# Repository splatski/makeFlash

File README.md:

# makeFlash
Soldering workshop board for Hobart Makers

# New Repository
Repositry is now at https://gitlab.com/HobartMakers/makeFlash

## Licence
Licensed under the TAPR Open Hardware License (www.tapr.org/OHL). The "license" folder within this repository also contains a copy of this license in plain text format.

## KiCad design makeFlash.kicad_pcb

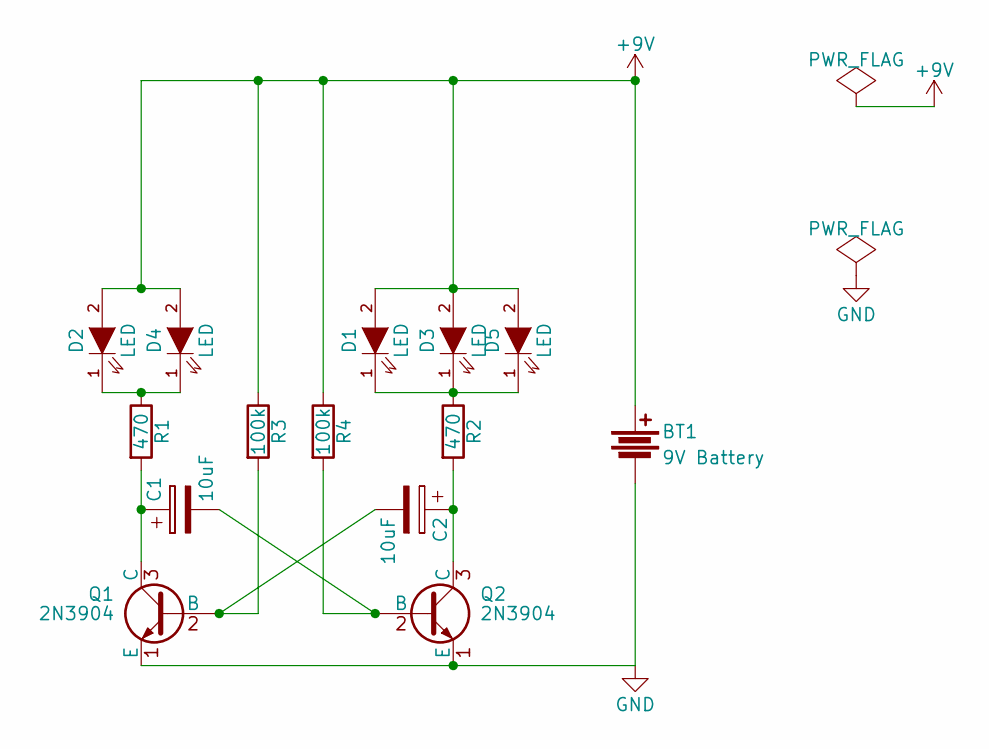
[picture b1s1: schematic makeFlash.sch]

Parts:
BT1: 9V Battery; Pin_Header_Straight_1x02_Pitch2.54mm
C1, C2: 10uF; CP_Radial_D5.0mm_P2.50mm
D1, D2, D3, D4, D5: LED; LED_Rectangular_W5.0mm_H2.0mm
Q1, Q2: 2N3904; TO-92_Rugged
R1, R2: 470; Resistor_Horizontal_RM10mm
R3, R4: 100k; Resistor_Horizontal_RM10mm

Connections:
+9V: BT1.1, D1.2 (A), D2.2 (A), D3.2 (A), D4.2 (A), D5.2 (A), R3.1, R4.1
GND: BT1.2, Q1.1 (E), Q2.1 (E)
unnamed: C1.1, Q1.3 (C), R1.2
unnamed: C1.2, Q2.2 (B), R4.2
unnamed: C2.1, Q2.3 (C), R2.2
unnamed: C2.2, Q1.2 (B), R3.2
unnamed: D1.1 (K), D3.1 (K), D5.1 (K), R2.1
unnamed: D2.1 (K), D4.1 (K), R1.1

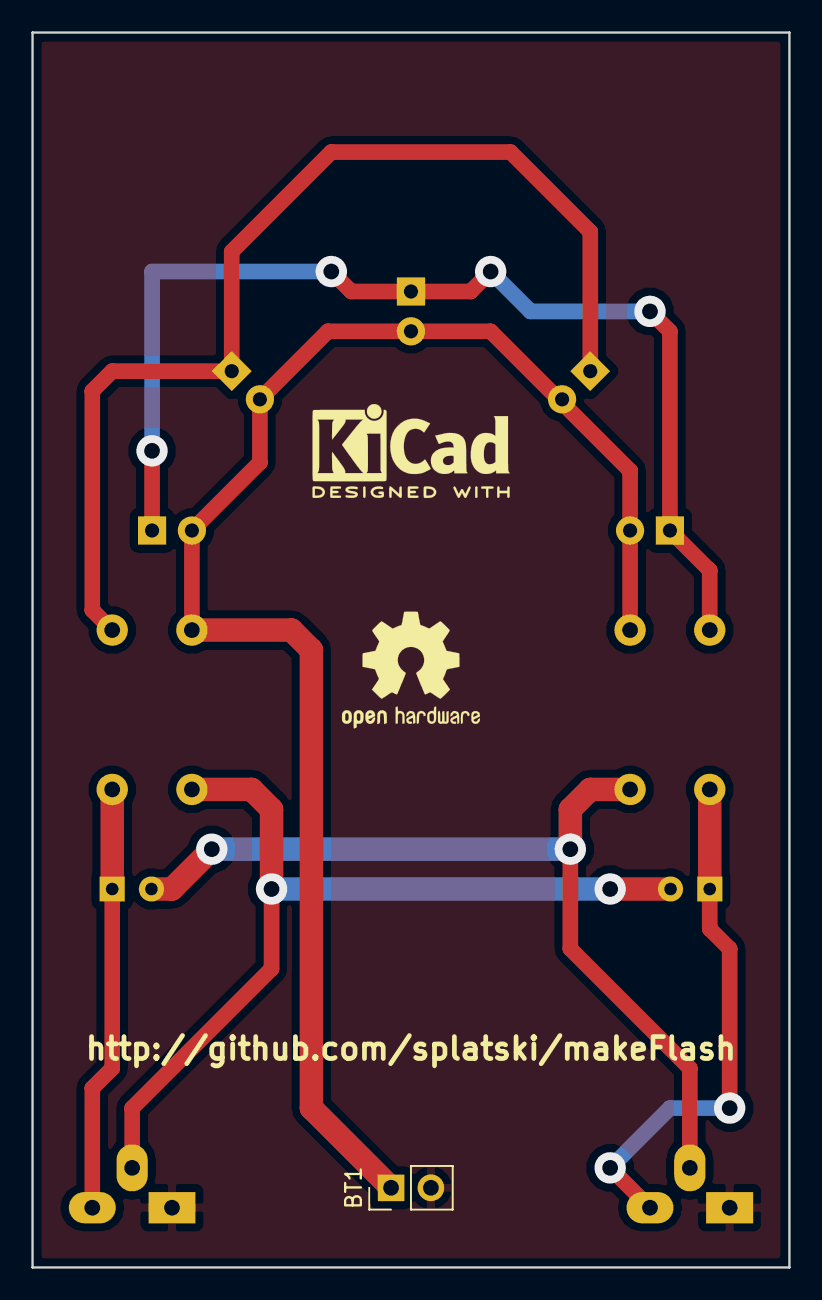
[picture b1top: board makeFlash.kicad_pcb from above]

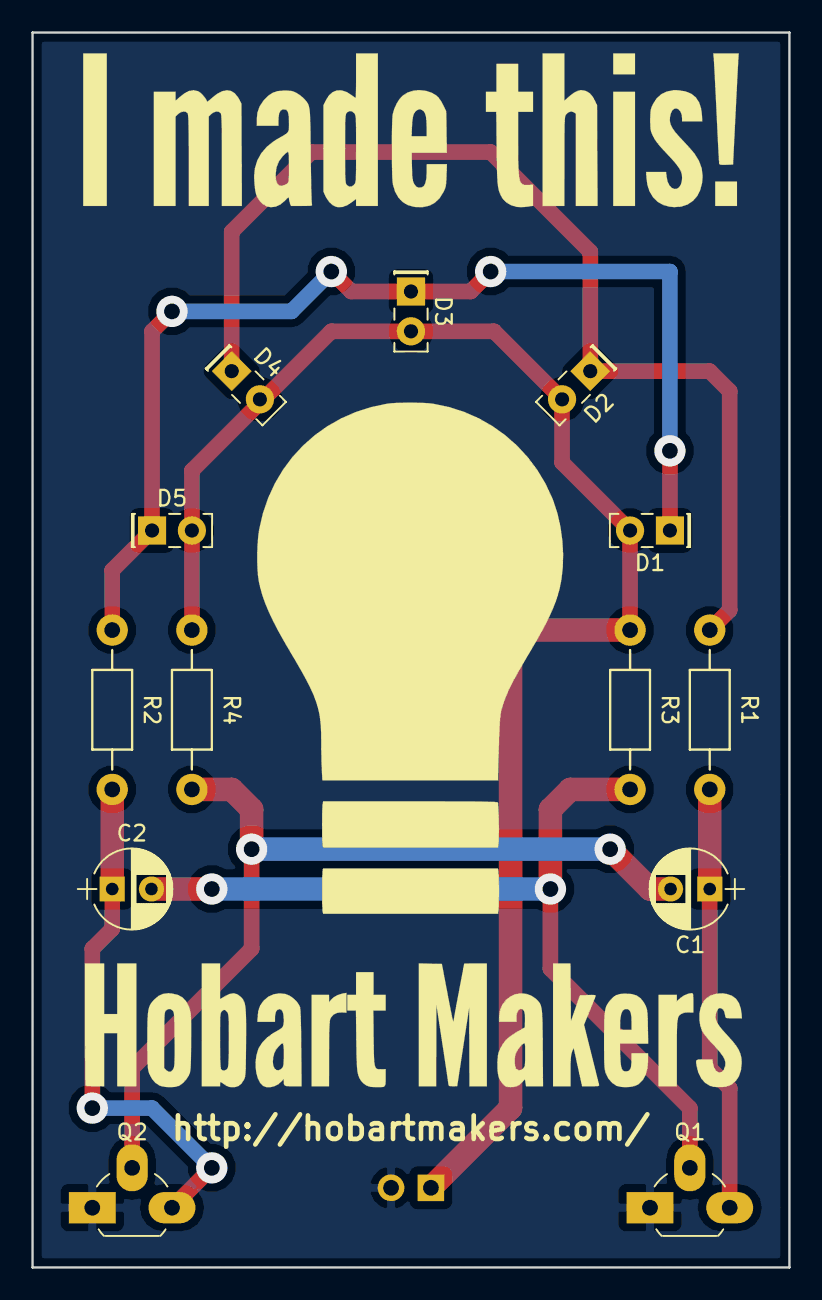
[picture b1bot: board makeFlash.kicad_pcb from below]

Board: 2 copper layers, 48.3 x 78.7 mm, 15 parts (13 on the bottom side), 8 nets.

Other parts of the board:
KiCadLogo: KiCad-Logo2_6mm_SilkScreen

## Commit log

2017-02-03 add the files
    generic useless git committ description on first adding files
2017-05-13 FAB Ready Version?
2017-05-13 Added 2 Board Panel
2017-05-13 update panel pcb
2017-05-16 slight reduction in size to definately fit within 100mm
2017-05-16 forgot to save changes first...
2017-05-17 fixed outline to cover board boards
2017-06-17 Added assembly photos taken by Scot F on Sat 17th June 2017
2022-11-01 Update Readme to point at new repo
